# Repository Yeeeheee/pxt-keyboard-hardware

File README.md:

# pxt-keyboard

Micro:bit keyboard expansion<br>
Software: https://github.com/Yeeeheee/pxt-keyboard

## Schematic

## Frontplate

## License
MIT

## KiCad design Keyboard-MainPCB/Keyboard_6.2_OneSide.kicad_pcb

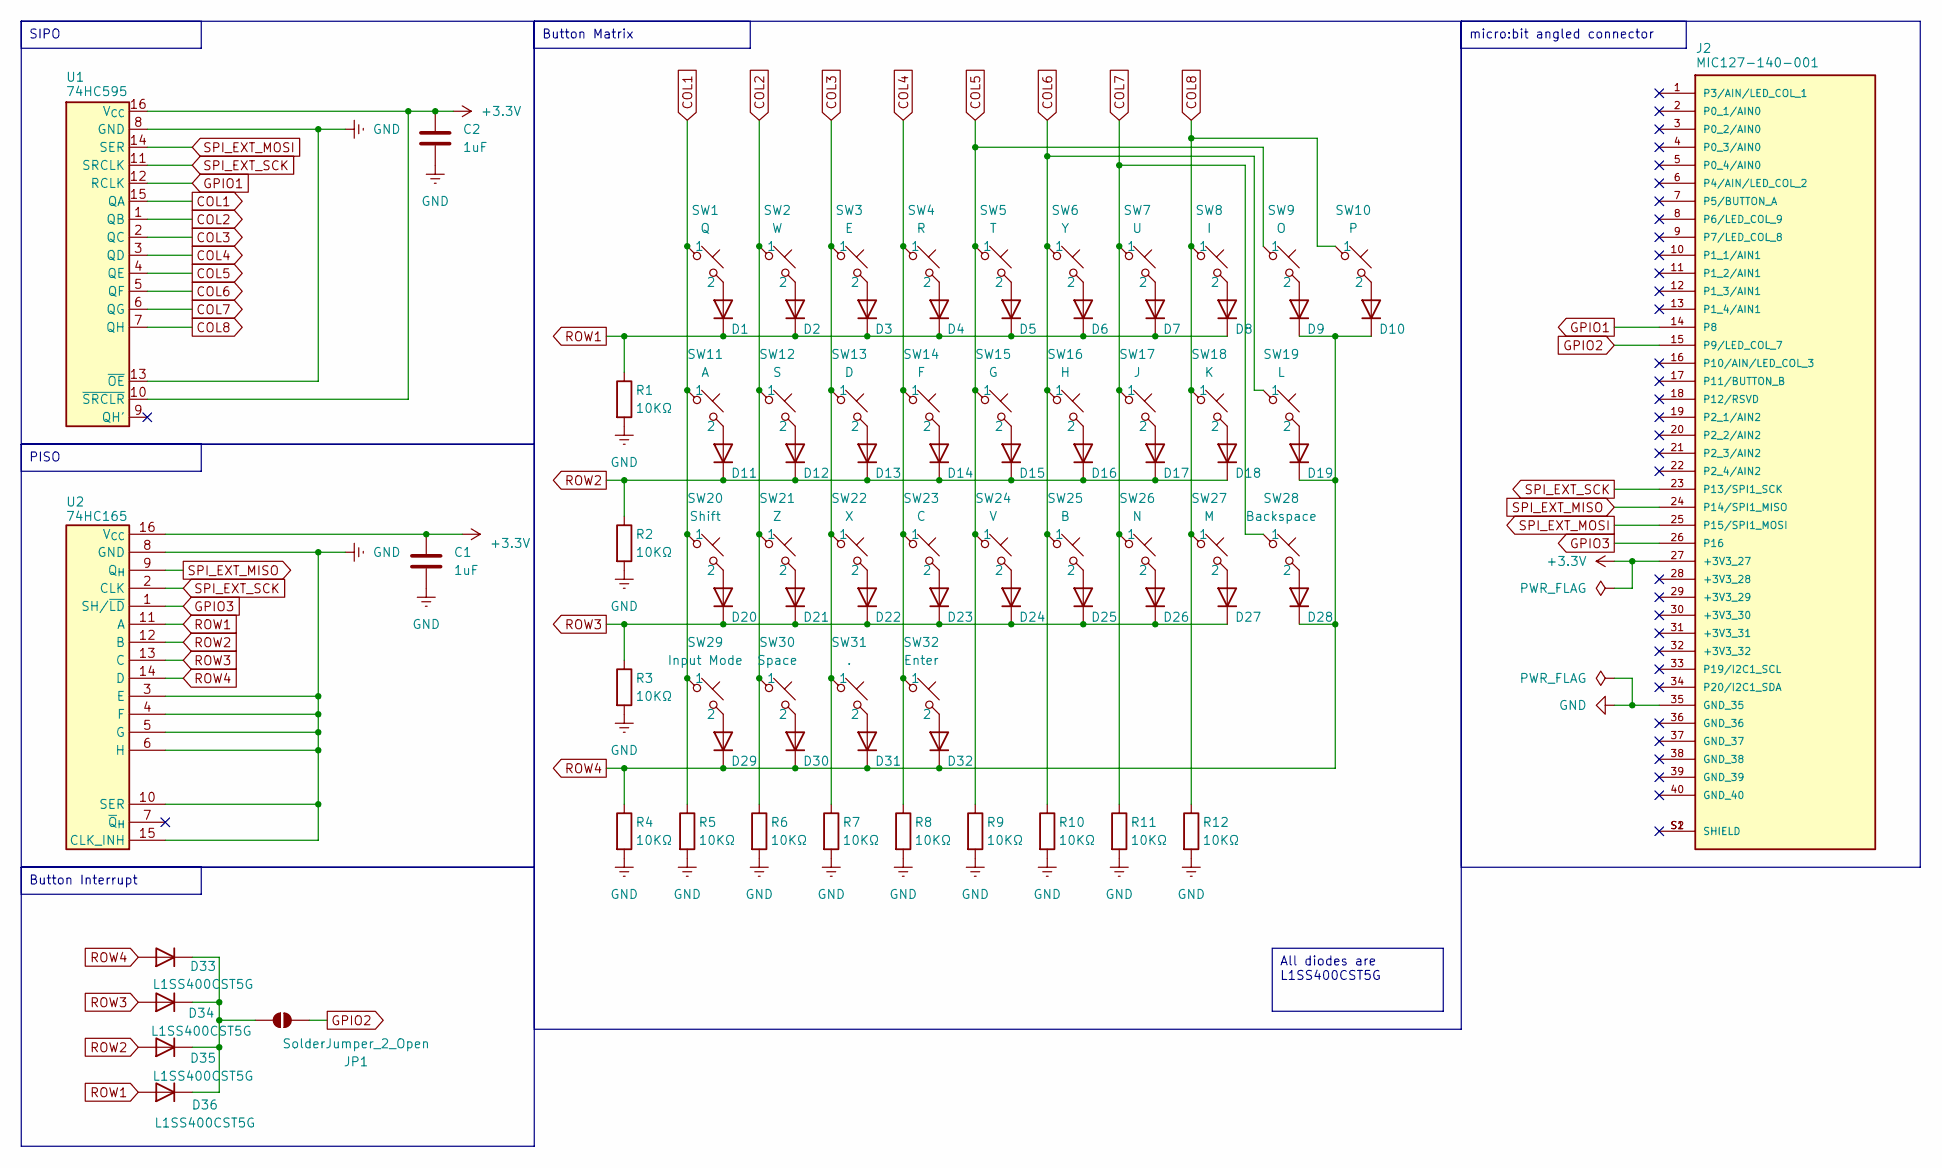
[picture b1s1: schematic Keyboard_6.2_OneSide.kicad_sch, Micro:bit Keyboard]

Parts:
C1, C2: 1uF; C_0603_1608Metric_Pad1.08x0.95mm_HandSolder; JLC part number C1592
D1, D2, D3, D4, D5, D6, D7, D8, D9, D10, D11, D12, D13, D14, D15, D16, D17, D18, D19, D20, D21, D22, D23, D24, D25, D26, D27, D28, D29, D30, D31, D32, D33, D34, D35, D36: L1SS400CST5G; D_SOD-923; JLC part number C383160
J2: MIC127-140-001; DONGGUAN_MIC127-140-001
JP1: SolderJumper_2_Open; SolderJumper-2_P1.3mm_Open_Pad1.0x1.5mm
R1, R2, R3, R4, R5, R6, R7, R8, R9, R10, R11, R12: 10KΩ; R_0402_1005Metric; JLC part number C25531
SW1: Q; KH-4.5X4.5X8H-STM; JLC part number C2837553
SW2: W; KH-4.5X4.5X8H-STM; JLC part number C2837553
SW3: E; KH-4.5X4.5X8H-STM; JLC part number C2837553
SW4: R; KH-4.5X4.5X8H-STM; JLC part number C2837553
SW5: T; KH-4.5X4.5X8H-STM; JLC part number C2837553
SW6: Y; KH-4.5X4.5X8H-STM; JLC part number C2837553
SW7: U; KH-4.5X4.5X8H-STM; JLC part number C2837553
SW8: I; KH-4.5X4.5X8H-STM; JLC part number C2837553
SW9: O; KH-4.5X4.5X8H-STM; JLC part number C2837553
SW10: P; KH-4.5X4.5X8H-STM; JLC part number C2837553
SW11: A; KH-4.5X4.5X8H-STM; JLC part number C2837553
SW12: S; KH-4.5X4.5X8H-STM; JLC part number C2837553
SW13: D; KH-4.5X4.5X8H-STM; JLC part number C2837553
SW14: F; KH-4.5X4.5X8H-STM; JLC part number C2837553
SW15: G; KH-4.5X4.5X8H-STM; JLC part number C2837553
SW16: H; KH-4.5X4.5X8H-STM; JLC part number C2837553
SW17: J; KH-4.5X4.5X8H-STM; JLC part number C2837553
SW18: K; KH-4.5X4.5X8H-STM; JLC part number C2837553
SW19: L; KH-4.5X4.5X8H-STM; JLC part number C2837553
SW20: Shift; KH-4.5X4.5X8H-STM; JLC part number C2837553
SW21: Z; KH-4.5X4.5X8H-STM; JLC part number C2837553
SW22: X; KH-4.5X4.5X8H-STM; JLC part number C2837553
SW23: C; KH-4.5X4.5X8H-STM; JLC part number C2837553
SW24: V; KH-4.5X4.5X8H-STM; JLC part number C2837553
SW25: B; KH-4.5X4.5X8H-STM; JLC part number C2837553
SW26: N; KH-4.5X4.5X8H-STM; JLC part number C2837553
SW27: M; KH-4.5X4.5X8H-STM; JLC part number C2837553
SW28: Backspace; KH-4.5X4.5X8H-STM; JLC part number C2837553
SW29: Input Mode; KH-4.5X4.5X8H-STM; JLC part number C2837553
SW30: Space; KH-4.5X4.5X8H-STM; JLC part number C2837553
SW31: .; KH-4.5X4.5X8H-STM; JLC part number C2837553
SW32: Enter; KH-4.5X4.5X8H-STM; JLC part number C2837553
U1: 74HC595; SOIC-16_3.9x9.9mm_P1.27mm; JLC part number C5947
U2: 74HC165; SOIC-16_3.9x9.9mm_P1.27mm; JLC part number C2863722

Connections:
+3.3V: C1.1, C2.1, J2.27 (+3V3_27), U1.10 (~SRCLR), U1.16 (V_{CC}), U2.16 (V_{CC})
COL1: R5.1, SW1.1, SW11.1, SW20.1, SW29.1, U1.15 (QA)
COL2: R6.1, SW2.1, SW12.1, SW21.1, SW30.1, U1.1 (QB)
COL3: R7.1, SW3.1, SW13.1, SW22.1, SW31.1, U1.2 (QC)
COL4: R8.1, SW4.1, SW14.1, SW23.1, SW32.1, U1.3 (QD)
COL5: R9.1, SW5.1, SW9.1, SW15.1, SW24.1, U1.4 (QE)
COL6: R10.1, SW6.1, SW16.1, SW19.1, SW25.1, U1.5 (QF)
COL7: R11.1, SW7.1, SW17.1, SW26.1, SW28.1, U1.6 (QG)
COL8: R12.1, SW8.1, SW10.1, SW18.1, SW27.1, U1.7 (QH)
GND: C1.2, C2.2, J2.35 (GND_35), R1.2, R2.2, R3.2, R4.2, R5.2, R6.2, R7.2, R8.2, R9.2, R10.2, R11.2, R12.2, U1.8 (GND), U1.13 (~OE), U2.3 (E), U2.4 (F), U2.5 (G), U2.6 (H), U2.8 (GND), U2.10 (SER), U2.15 (CLK_INH)
GPIO1: J2.14 (P8), U1.12 (RCLK)
GPIO2: J2.15 (P9/LED_COL_7), JP1.1 (A)
GPIO3: J2.26 (P16), U2.1 (SH/~LD)
unnamed: D1.2 (A), SW1.2
unnamed: D2.2 (A), SW2.2
unnamed: D3.2 (A), SW3.2
unnamed: D4.2 (A), SW4.2
unnamed: D5.2 (A), SW5.2
unnamed: D6.2 (A), SW6.2
unnamed: D7.2 (A), SW7.2
unnamed: D8.2 (A), SW8.2
unnamed: D9.2 (A), SW9.2
unnamed: D10.2 (A), SW10.2
unnamed: D11.2 (A), SW11.2
unnamed: D12.2 (A), SW12.2
unnamed: D13.2 (A), SW13.2
unnamed: D14.2 (A), SW14.2
unnamed: D15.2 (A), SW15.2
unnamed: D16.2 (A), SW16.2
unnamed: D17.2 (A), SW17.2
unnamed: D18.2 (A), SW18.2
unnamed: D19.2 (A), SW19.2
unnamed: D20.2 (A), SW20.2
unnamed: D21.2 (A), SW21.2
unnamed: D22.2 (A), SW22.2
unnamed: D23.2 (A), SW23.2
unnamed: D24.2 (A), SW24.2
unnamed: D25.2 (A), SW25.2
unnamed: D26.2 (A), SW26.2
unnamed: D27.2 (A), SW27.2
unnamed: D28.2 (A), SW28.2
unnamed: D29.2 (A), SW29.2
unnamed: D30.2 (A), SW30.2
unnamed: D31.2 (A), SW31.2
unnamed: D32.2 (A), SW32.2
unnamed: D33.1 (K), D34.1 (K), D35.1 (K), D36.1 (K), JP1.2 (B)
ROW1: D1.1 (K), D2.1 (K), D3.1 (K), D4.1 (K), D5.1 (K), D6.1 (K), D7.1 (K), D8.1 (K), D36.2 (A), R1.1, U2.11 (A)
ROW2: D11.1 (K), D12.1 (K), D13.1 (K), D14.1 (K), D15.1 (K), D16.1 (K), D17.1 (K), D18.1 (K), D35.2 (A), R2.1, U2.12 (B)
ROW3: D20.1 (K), D21.1 (K), D22.1 (K), D23.1 (K), D24.1 (K), D25.1 (K), D26.1 (K), D27.1 (K), D34.2 (A), R3.1, U2.13 (C)
ROW4: D9.1 (K), D10.1 (K), D19.1 (K), D28.1 (K), D29.1 (K), D30.1 (K), D31.1 (K), D32.1 (K), D33.2 (A), R4.1, U2.14 (D)
SPI_EXT_MISO: J2.24 (P14/SPI1_MISO), U2.9 (Q_{H})
SPI_EXT_MOSI: J2.25 (P15/SPI1_MOSI), U1.14 (SER)
SPI_EXT_SCK: J2.23 (P13/SPI1_SCK), U1.11 (SRCLK), U2.2 (CLK)

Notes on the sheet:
micro:bit angled connector
Button Matrix
Button Interrupt
All diodes are L1SS400CST5G
PISO
SIPO

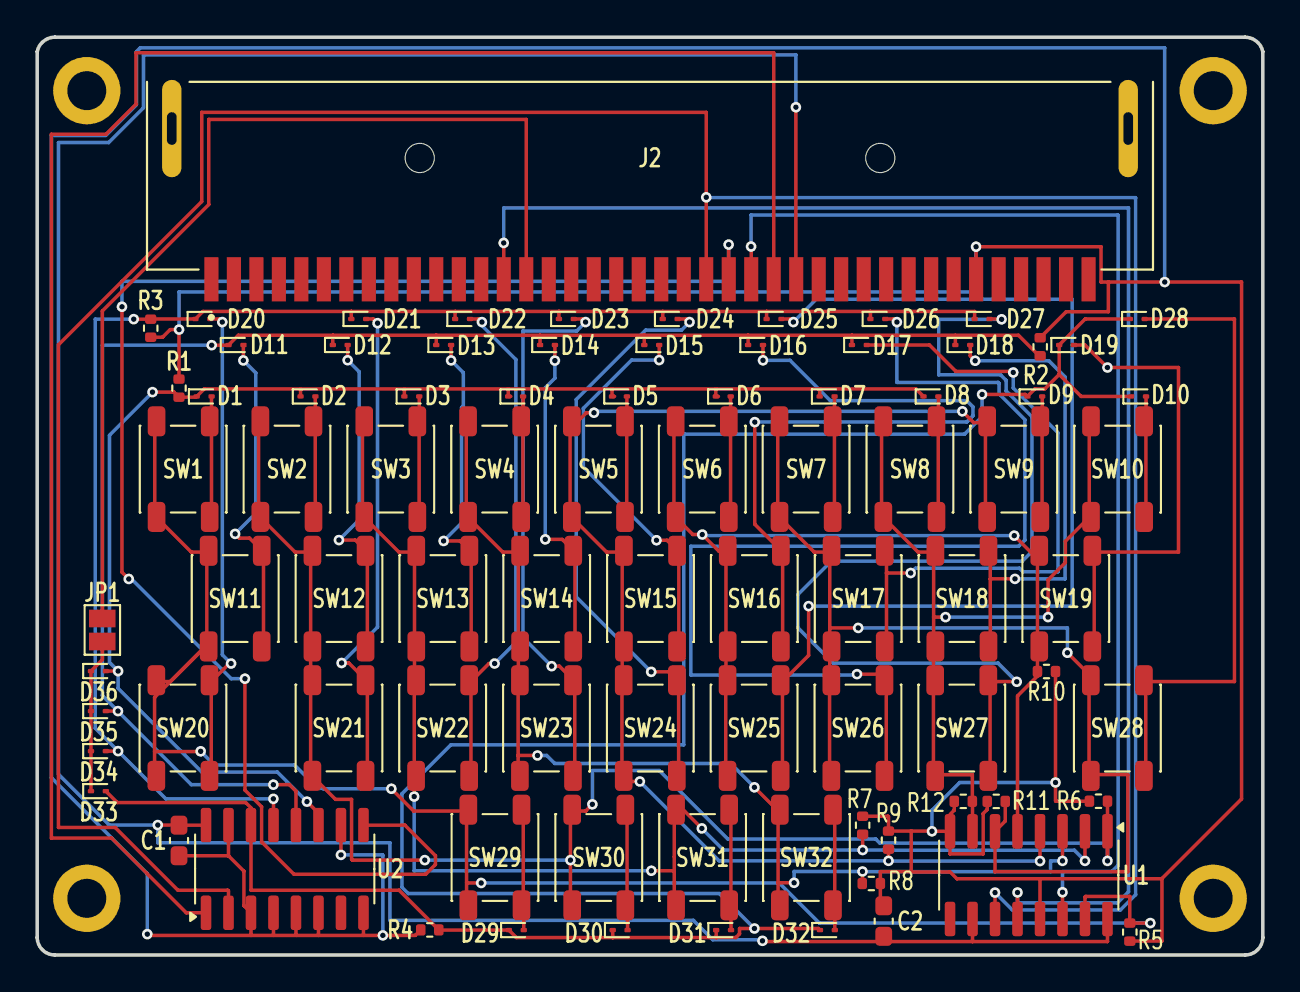
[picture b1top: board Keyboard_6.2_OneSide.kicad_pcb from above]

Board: 2 copper layers, 69.2 x 51.8 mm, 86 parts (0 on the bottom side), 53 nets.

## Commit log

2025-03-20 Add files via upload
    Hardware design for the micro:bit keyboard
2025-05-26 Add images
